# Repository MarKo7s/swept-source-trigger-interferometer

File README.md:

# Swept-source interferometer camera trigger (k-clock)

## Project: DIY k-clock for laser-sweep synchronization

This repository has what you need to build a **k-clock** for applications such as optical coherence tomography (OCT):

1. PCB schematics
2. Firmware for trigger detection
3. SCPI command interface and Python package (**pySSTri**)

You still need the external optics and detectors: swept laser, interferometer, and balanced photodiode (BPD).

## What is a k-clock?

A **k-clock** (swept-source interferometer trigger) produces equally spaced optical-frequency samples across a fixed bandwidth by detecting zero-crossings of the interferogram $V_{\mathrm{BPD}}(\nu)$ and emitting a TTL (~5 V) edge at each crossing. Those edges mark known optical frequencies $\nu$ (or wavelengths) along the sweep.

The raw interferogram rate is set by the optical path-length mismatch between the interferometer arms. Signal conditioning and trigger generation run on a **PSoC 5LP** — a programmable SoC with a 32-bit MCU, configurable analog blocks, and programmable digital logic on one chip. This board digitally **frequency-divides** the BPD/camera trigger train by an arbitrary integer in hardware (no CPU in the divider path). Hosts talk over UART (115200 baud, CRLF). The Python package **pySSTri** wraps that protocol.

## Interferometer working principle

The laser is launched into one port of a 50/50 coupler and sweeps optical frequency $\nu$ at constant speed across a bandwidth $\Delta\nu$. After the first coupler, the field $E_{\mathrm{in}}(\nu)$ is split into $E_1(\nu)$ and $E_2(\nu)$ and recombined in a second coupler. One arm includes an extra fibre delay of length $l_{\mathrm{DLY}}$.

After balanced photodetection (BPD), TIA, and voltage amplification, the electrical interferogram is:

$$
V_{\mathrm{BPD}}(\nu) = V_0 \cdot \cos\left(2\pi\cdot\frac{1}{\mathrm{FSR}}\cdot\nu\right)
$$

$V_{\mathrm{BPD}}$ crosses zero at equally spaced optical frequencies $\nu_n$. The spacing is the **free spectral range**

$$
\mathrm{FSR} = \frac{c}{n\,l_{\mathrm{DLY}}}
\quad [\mathrm{Hz}]
$$

where $\nu$ is optical frequency, $c$ is the vacuum speed of light, and $n$ is the refractive index of the fibre (so the speed in the medium is $c/n$). Those zero crossings define the natural k-clock grid (panel a below).

*Swept-laser Mach–Zehnder interferometer used as a k-clock.*

The BPD sinusoid is conditioned into a TTL (0 → +5 V) pulse train with the same period $\mathrm{FSR}$. Each rising edge at $\nu_n$ can trigger a camera frame (panel b). The number of frames over the sweep is

$$
D_{\nu} = \frac{\Delta\nu}{\mathrm{FSR}}.
$$

This board digitally divides that TTL by an integer $Q$ in hardware, so only every $Q$-th edge is passed to the camera while keeping the same optical-frequency locations. Example with $Q = 4$: twelve raw edges become four divided triggers (panel c).

*(a) Raw BPD interferogram. (b) Rising-edge TTL after conditioning. (c) Same train after divide-by-4 ($Q=4$).*

---

## Installation (Python)

**Tagged release:**

```bash
pip install "pySSTri @ git+https://github.com/MarKo7s/swept-source-trigger-interferometer.git@v1.1.1"
```

With notebook extras:

```bash
pip install "pySSTri[notebooks] @ git+https://github.com/MarKo7s/swept-source-trigger-interferometer.git@v1.1.1"
```

**Editable (dev):**

```bash
git clone git@github.com:MarKo7s/swept-source-trigger-interferometer.git
cd swept-source-trigger-interferometer
pip install -e ".[notebooks]"
```

**Conda:**

```bash
conda create -n pySSTri_env python=3.11 -y
conda activate pySSTri_env
pip install -e ".[notebooks]"
python -m ipykernel install --user --name pySSTri_env --display-name "Python (pySSTri_env)"
```

---

## How to operate

There are two layers:

| Layer | Use when |
| ----- | -------- |
| **Firmware (UART / SCPI)** | Any host language, raw serial, or writing your own driver |
| **Python (`pySSTri`)** | Lab scripts / notebooks — preferred for day-to-day use |

Same baud rate (115200) and the same commands either way. Python methods map 1:1 onto SCPI (e.g. `SetFreqDivision(4)` → `SIG:TRIG:DIV 4`).

The board does **not** start the laser. The laser (or your control software) asserts the sweep gate `sw`; the PSoC only measures and emits camera TTL. How the **host** keeps up with sweeps falls into two patterns.

### Mode A — Asynchronous (poll / pull)

Laser sweeps on its own schedule. The host configures the board once (`SIG:TRIG:DIV`, maybe encoding), then **queries when convenient**: status, last count, frequency, or pull timestamps **after** the sweep (idle). No blocking wait on UART notify.

Typical uses: debugging, notebook checks, slow loops, “did the last sweep look OK?”

```text
  Laser ──► sw low ──► …sweep… ──► sw high
  Host  ·····························► GetSweepStatus? / GetTimestamps?
                                       (poll when idle)
```

```python
board.SetModeNormal()                 # SYS:TRIG:NOT OFF — no end-of-sweep UART dump
board.SetFreqDivision(2)
# … laser sweeps somehow …
while board.GetSweepStatus() == "1":  # optional: wait until idle
    pass
ts, ov, fc = board.GetTimestamps()    # pull buffer after the sweep
```

While `sw` is low, most commands return `ERROR: 1`; `LASER:SWE:STATUS?` still works.

### Mode B — Synchronous (notify / wait)

Enable end-of-sweep notify (`SYS:TRIG:NOT TIME|COUNT|FREQ|ALL|TIMESTAMP`). When each sweep finishes, the board **pushes** a line (or a `TSU` frame) on UART.

Typical pattern: a **watcher thread** blocks on `waitForSignal()` / `readline`; the **main thread** runs the laser (or other work) and syncs with `done.wait()` when the notify arrives — so UART wait does not block the main thread.

```mermaid
sequenceDiagram
    participant Main as Main thread
    participant Watch as Watcher thread
    participant Board as PSoC board
    participant Laser

    Main->>Board: set notify COUNT
    Main->>Watch: start waitForSignal
    Main->>Laser: start_sweep
    Laser->>Board: sw low then high
    Board-->>Watch: notify line
    Watch->>Main: done.set
    Note over Main: done.wait returns
```

```python
import threading

done = threading.Event()

def watch_sweep_done():
    board.waitForSignal()   # blocks only this thread on UART notify
    done.set()

board.SetModeCount()
board.flushSerialBuffer()
threading.Thread(target=watch_sweep_done, daemon=True).start()

laser.start_sweep()         # main owns the sweep / other work
done.wait(timeout=30.0)     # sync when board says sweep finished
```

For timestamp notify on the watcher thread, use `waitTimestamps()` instead of `waitForSignal()`.

| Aspect | Mode A (async) | Mode B (sync) |
| ------ | -------------- | ------------- |
| Notify | `SYS:TRIG:NOT OFF` | `TIME` / `COUNT` / `FREQ` / `ALL` / `TIMESTAMP` |
| Host API | `GetSweepStatus`, `GetTimestamps`, … | watcher: `waitForSignal` / `waitTimestamps`; main: `Event.wait` |
| Timing | Host decides when to ask | Main syncs when end-of-sweep notify arrives |
| Best for | Inspection, scripts | Acquisition loops without blocking main on UART |

Always `flushSerialBuffer()` after changing notify mode so a stale line does not satisfy the next `wait`.

---

## Firmware

### Which project to flash

Firmware is **variant-specific** (polarity / laser). Pick the folder under `psoc5/firmware/` that matches your hardware:

| Project | Role |
| ------- | ---- |
| `PSOC_trigger_firmware_Trigger_Polarity_Low` | **Production** (FW 1.3.1) — active-low LEVEL sweep gate + timestamps |
| `PSOC_trigger_firmware_DEBUG` | Experimental |

Production firmware is tuned for an **active-low** sweep gate. Other lasers or trigger polarities can be supported on request (see [Contact](#contact)).

### Install tools and flash

1. Install [PSoC Programmer](https://softwaretools.infineon.com/tools/com.ifx.tb.tool.psocprogrammer). If it asks to update the kit / MiniProg firmware, allow that, then **close** Programmer.
2. Install [PSoC Creator](https://www.infineon.com/cms/en/design-support/tools/sdk/psoc-software/psoc-creator/) (Cypress / Infineon).
3. In Creator, open the workspace for the project you chose, e.g. production:

   `psoc5/firmware/PSOC_trigger_firmware_Trigger_Polarity_Low/Trigger_PSOC5.cywrk`

4. Connect the board (USB / MiniProg as wired on your PCB).
5. Build if needed, then **Debug → Program**.
6. Verify over UART (115200 baud, CRLF): send `*IDN?` — it should report firmware version and date (e.g. FW 1.3.1). With Python: `board.ID()` after `connect()`.

Host control after flashing: see [Installation (Python)](#installation-python) and `trigger_example.ipynb`.

### Sweep gate (Polarity Low)

The sweep input `sw` is **active-low LEVEL**, not a falling-edge pulse:

- **Sweeping** while `sw` is held low
- **Idle** while `sw` is high

While sweeping, most commands return `ERROR: 1`. Exception: `LASER:SWE:STATUS?` (`1` = sweeping, `0` = idle).

### Command reference

Lines end with `\r\n`. Sets reply `OK` (or `OK - WARNING: …`). Queries reply a value. Errors: `ERROR: 0` (bad command), `ERROR: 1` (busy / sweeping).

| Command                            | Meaning                                       |
| ---------------------------------- | --------------------------------------------- |
| `*IDN?`                            | Identify                                      |
| `SIG:TRIG:DIV <n>` / `?`           | Camera trigger divider (default `2`)          |
| `SIG:TRIG:EVENTS:COUNT?`           | Trigger count last sweep                      |
| `SIG:TRIG:EVENTS:FREQ?`            | Mean trigger rate [Hz] (first→last timestamp) |
| `SIG:TRIG:TIMESTAMP?`              | Pull timestamp buffer (idle only)             |
| `LASER:SWE:TIME?`                  | Sweep duration [µs]                           |
| `LASER:SWE:COUNT?` / `0` / `RESET` | Cumulative sweeps / clear                     |
| `LASER:SWE:STATUS?`                | `1` sweeping / `0` idle                       |
| `SYS:TRIG:NOT <mode>` / `?` | Notify mode: `OFF`, `TIME`, `COUNT`, `FREQ`, `ALL`, `TIMESTAMP` |
| `SYS:TIMESTAMP:DELTAENC <mode>` / `?` | Packing: `OFF`, `UINT8`, `UINT16` (aliases `0`, `1`, `2`) |

### Timestamps

Each camera-trigger edge is stamped by a 24 MHz Timer during the sweep (ISR fill, up to **4000** samples). Values are **µs from sweep start**.

**Typical flow**

1. Optionally set packing: `SYS:TIMESTAMP:DELTAENC UINT16` (see delta encoding below).
2. Run a sweep (or enable `SYS:TRIG:NOT TIMESTAMP` for an automatic dump each sweep).
3. When idle: `SIG:TRIG:TIMESTAMP?` → one ASCII header line + binary payload.

**Wire header** (always the same fields):

```
TSU <n> <ov> <fc> <t0> <enc>\r\n
```

| Field | Meaning                                         |
| ----- | ----------------------------------------------- |
| `n`   | Number of timestamps                            |
| `ov`  | `1` if buffer overflowed or a delta was clamped |
| `fc`  | Hardware event count for the sweep              |
| `t0`  | First sample [µs]                               |
| `enc` | Packing mode (`0` / `1` / `2`) — always last    |

Then the **payload** depends on `enc`:

| `enc` | Name           | Payload                     | Host reconstruct           |
| ----- | -------------- | --------------------------- | -------------------------- |
| `0`   | OFF (absolute) | `n × uint32` LE absolute µs | use as-is                  |
| `1`   | UINT8 deltas   | `(n−1) × uint8` gaps        | `t[0]=t0`, then accumulate |
| `2`   | UINT16 deltas  | `(n−1) × uint16` LE gaps    | same accumulate            |

Delta encoding shrinks UART traffic when consecutive gaps are small. Choose a mode whose **max gap** fits your laser:

| Mode   | Max gap       | Safe if trigger rate |
| ------ | ------------- | -------------------- |
| UINT8  | 255 µs        | **≥ ~3.9 kHz**       |
| UINT16 | 65535 µs      | **≥ ~15 Hz**         |
| OFF    | (full uint32) | any                  |

If a gap is too large for the mode, firmware **clamps** it and sets `ov=1` (lossy). For ~3 kHz SS sources, prefer **UINT16** or **OFF**, not UINT8.

Setting the mode returns a warning with those limits, e.g.:

```
SYS:TIMESTAMP:DELTAENC 2
→ OK - WARNING: max_dt_us=65535 min_freq_hz=15
```

**False triggers:** noisy interferogram / BPD edges can create extra timestamps. A hardware **deglitch** filter is planned but not in this firmware yet — raise the comparator threshold / SNR, or filter bad gaps in software for now.

### Hardware (PCB)

Eagle schematics and board files: `pcb/Eagle_project/Trigger_PSOC5LP`.

---

## Python interface (`pySSTri`)

Example notebook: `trigger_example.ipynb`.

### Connect

```python
from pySSTri import SSTriggerInterferometer

board = SSTriggerInterferometer()   # or COM="COM6"
board.connect()                     # autodiscovers via *IDN? if needed
board.discoverMethods()             # list wrappers
print(board.ID())
```

### Everyday control

See [How to operate](#how-to-operate) for async poll vs sync wait. Short sync example:

```python
board.SetFreqDivision(2)
board.SetModeCount()                # notify: trigger count each sweep
board.flushSerialBuffer()
print(board.waitForSignal())        # blocks for next notify line
print(board.GetSweepStatus())       # "0" / "1"
print(board.GetFrequency(), board.GetSweepTime())
```

### Timestamps (decoded to absolute µs for you)

```python
board.SetTimestampsEncoding(2)      # UINT16 deltas on the wire (FW aliases OK)
# board.SetModeTimestamp()          # optional: auto-dump each sweep
# ts, ov, fc = board.waitTimestamps()

ts, ov, fc = board.GetTimestamps()  # after a sweep, while idle
# ts: uint32 array [µs], regardless of enc in the header
```

`GetTimestamps` / `waitTimestamps` read the `TSU` header’s `enc` field and unpack the payload — you always get absolute times.

---

## Repository layout

```
pySSTri/          Python package
psoc5/firmware/   PSoC Creator projects
pcb/              Eagle schematics
trigger_example.ipynb
scripts/release.py
CITATION.cff      GitHub / Zenodo cite metadata
CITATION.bib      BibTeX for manuscripts
```

---

## Developer notes

### Versioning

The package version is defined in **one place only**: `pyproject.toml` → `[project].version`.

Do **not** edit `pySSTri/__init__.py` on each release. `pySSTri.__version__` is read from pip metadata after install (`importlib.metadata`).

Check the installed version:

```bash
pip show pySSTri
python -c "import pySSTri; print(pySSTri.__version__)"
```

Use [semantic versioning](https://semver.org/): `MAJOR.MINOR.PATCH`.

Firmware has its own identity (`FW_VERSION` / `FW_DATE` in `main.c`, reported by `*IDN?`). Bump that when you change the PSoC image; it is independent of the pySSTri package version.

Default git branch is `main`.

### Releasing a new version

1. Add a `## [X.Y.Z] - YYYY-MM-DD` section at the top of `CHANGELOG.md` (keep `## [Unreleased]` above it for WIP notes).
2. Set `version = "X.Y.Z"` in `pyproject.toml`.
3. Commit everything (clean working tree).
4. From the repo root:

```bash
python scripts/release.py --from-changelog
```

The script reads the version from `pyproject.toml`, pushes `main`, creates annotated git tag `vX.Y.Z`, and pushes the tag. With `--from-changelog`, the tag message is taken from the matching `CHANGELOG.md` section. Override with `--message "..."` if needed.

Dry run (no git changes):

```bash
python scripts/release.py --from-changelog --dry-run
```

Optional GitHub Release page (`gh` CLI):

```bash
gh release create vX.Y.Z --title "pySSTri X.Y.Z" --notes-file CHANGELOG.md
```

After release, others install with:

```bash
pip install "pySSTri @ git+https://github.com/MarKo7s/swept-source-trigger-interferometer.git@vX.Y.Z"
```

**Requirements:** clean working tree; tag `vX.Y.Z` must not already exist on GitHub.

## Contact

Marcos Maestre Morote — [m.maestremorote@uq.edu.au](mailto:m.maestremorote@uq.edu.au)

Questions, bug reports, or requests to adapt the firmware to a different swept laser / sweep-gate polarity are welcome.

## License

This project is licensed under the [MIT License](LICENSE). Copyright (c) 2026 Marcos Maestre Morote.

## Citation

Use these identifiers in the manuscript so Methods, Supplementary, and the bibliography stay consistent.

### Versions to tag

| Item | Value to cite |
| ---- | ------------- |
| Software / archive | **pySSTri v1.1.1** |
| Git tag | `v1.1.1` |
| Zenodo DOI | [10.5281/zenodo.21639219](https://doi.org/10.5281/zenodo.21639219) |
| Production firmware | **Polarity Low 1.3.1** (`*IDN?` / `board.ID()`) |
| BibTeX key | `MaestreMorote2026pySSTri` (see [`CITATION.bib`](CITATION.bib)) |

### BibTeX (drop into your `.bib`)

```bibtex
@software{MaestreMorote2026pySSTri,
  author       = {Maestre Morote, Marcos},
  title        = {{Swept-source interferometer camera trigger (pySSTri)}},
  year         = {2026},
  publisher    = {Zenodo},
  version      = {v1.1.1},
  doi          = {10.5281/zenodo.21639219},
  url          = {https://doi.org/10.5281/zenodo.21639219},
  note         = {Firmware Polarity Low 1.3.1; source https://github.com/MarKo7s/swept-source-trigger-interferometer}
}
```

LaTeX: `\cite{MaestreMorote2026pySSTri}`. Word / EndNote: import the DOI or use the formatted reference below.

### Formatted reference

> Marcos Maestre Morote. *Swept-source interferometer camera trigger (pySSTri)*. Zenodo (2026). Version v1.1.1. https://doi.org/10.5281/zenodo.21639219

### Paste into Methods

Adapt to your tense/house style; keep the cite key and versions:

> Wavelength / optical-frequency sampling during each laser sweep was provided by a fibre Mach–Zehnder k-clock interferometer and balanced photodiode. Zero-crossing edges were conditioned into a TTL train and divided by an integer $Q$ in hardware on a custom PSoC 5LP camera-trigger board. Instrument control used the open-source package pySSTri (v1.1.1; firmware Polarity Low 1.3.1) \cite{MaestreMorote2026pySSTri}.

### Paste into Supplementary

> **Trigger interferometer and camera timing.** The auxiliary k-clock path is a fibre Mach–Zehnder interferometer with fixed delay; the balanced-photodiode interferogram is converted to a TTL pulse train at the free-spectral-range spacing. A PSoC 5LP board performs hardware frequency division of that train and exposes sweep timing over UART (115200 baud, SCPI-like commands). Host software was **pySSTri** v1.1.1 (GitHub tag `v1.1.1`), archived at Zenodo (DOI: 10.5281/zenodo.21639219), with production firmware **Trigger Polarity Low** 1.3.1. Schematics, firmware, and the Python interface are available under the MIT License at https://github.com/MarKo7s/swept-source-trigger-interferometer. Further protocol details (notify vs poll modes, timestamp frames) are documented in the repository README.

GitHub also exposes **Cite this repository** from [`CITATION.cff`](CITATION.cff).

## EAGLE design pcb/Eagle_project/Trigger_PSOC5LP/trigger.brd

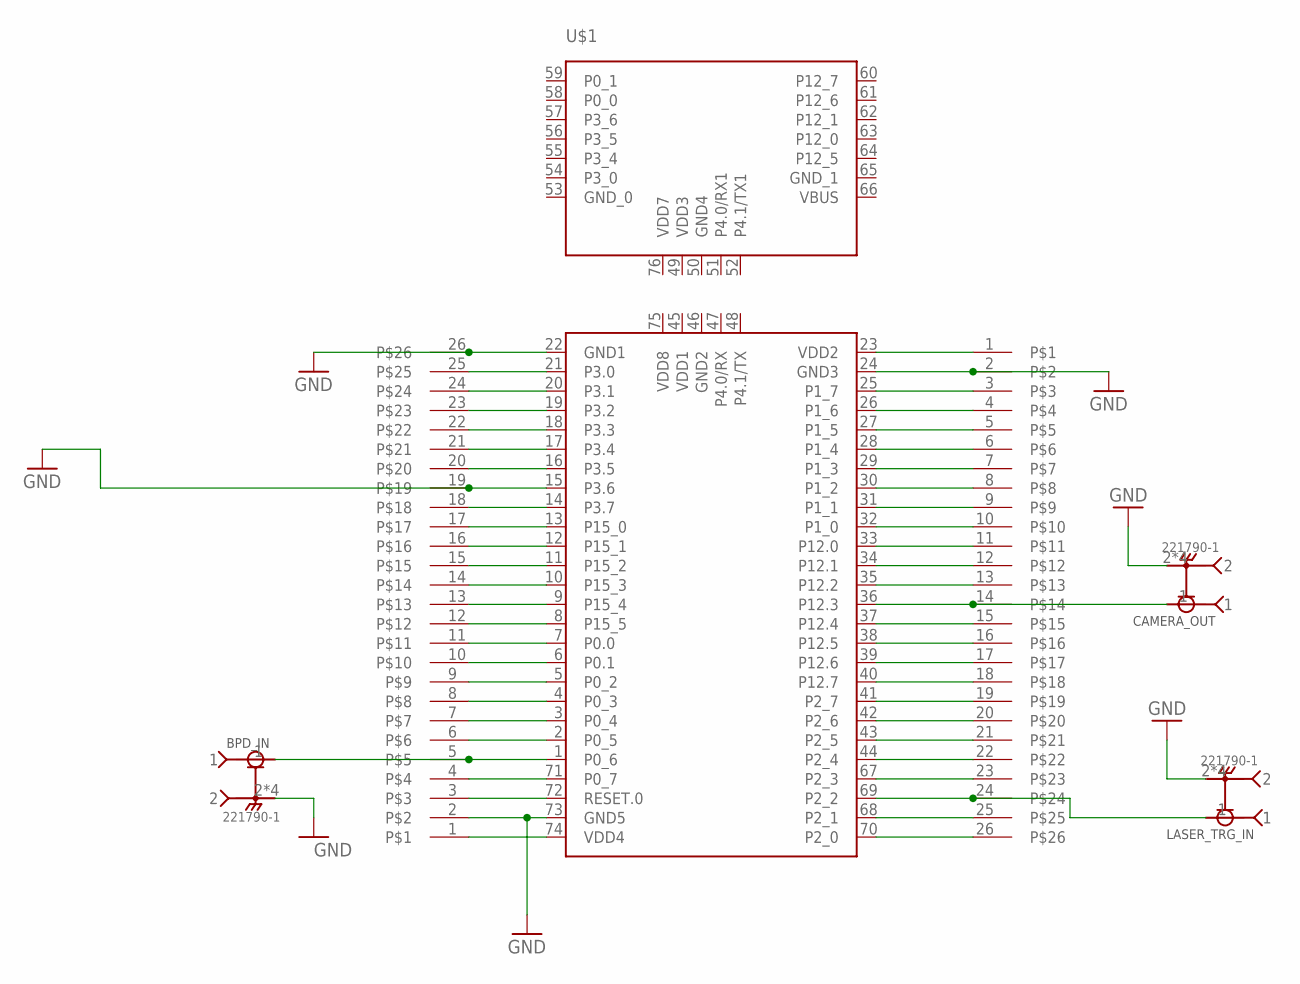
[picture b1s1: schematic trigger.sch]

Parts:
BPD_IN: 221790-1; TE_221790-1
CAMERA_OUT: 221790-1; TE_221790-1
LASER_TRG_IN: 221790-1; TE_221790-1
U$1: CY8CKIT-049-42XX
U$2, U$3: PINHEADER_PSOC5LP; PINHEADER

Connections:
GND: BPD_IN.2, BPD_IN.3 (2), BPD_IN.4 (2), BPD_IN.5 (2), CAMERA_OUT.2, CAMERA_OUT.3 (2), CAMERA_OUT.4 (2), CAMERA_OUT.5 (2), LASER_TRG_IN.2, LASER_TRG_IN.3 (2), LASER_TRG_IN.4 (2), LASER_TRG_IN.5 (2), U$1.15 (P3.6), U$1.22 (GND1), U$1.24 (GND3), U$1.73 (GND5), U$2.2, U$2.19, U$2.26, U$3.2
unnamed: U$1.8 (P15_5), U$2.12
unnamed: U$1.72 (RESET.0), U$2.3
unnamed: U$1.21 (P3.0), U$2.25
unnamed: U$1.20 (P3.1), U$2.24
unnamed: U$1.19 (P3.2), U$2.23
unnamed: U$1.18 (P3.3), U$2.22
unnamed: U$1.17 (P3.4), U$2.21
unnamed: U$1.16 (P3.5), U$2.20
unnamed: U$1.67 (P2_3), U$3.23
unnamed: U$1.14 (P3.7), U$2.18
unnamed: U$1.13 (P15_0), U$2.17
unnamed: U$1.12 (P15_1), U$2.16
unnamed: U$1.11 (P15_2), U$2.15
unnamed: U$1.10 (P15_3), U$2.14
unnamed: U$1.9 (P15_4), U$2.13
unnamed: U$1.7 (P0.0), U$2.11
unnamed: U$1.5 (P0_2), U$2.9
unnamed: U$1.4 (P0_3), U$2.8
unnamed: U$1.3 (P0_4), U$2.7
unnamed: U$1.2 (P0_5), U$2.6
unnamed: BPD_IN.1, U$1.1 (P0_6), U$2.5
unnamed: U$1.71 (P0_7), U$2.4
unnamed: U$1.6 (P0.1), U$2.10
unnamed: U$1.74 (VDD4), U$2.1
unnamed: U$1.23 (VDD2), U$3.1
unnamed: U$1.25 (P1_7), U$3.3
unnamed: U$1.26 (P1_6), U$3.4
unnamed: U$1.27 (P1_5), U$3.5
unnamed: U$1.28 (P1_4), U$3.6
unnamed: U$1.29 (P1_3), U$3.7
unnamed: U$1.30 (P1_2), U$3.8
unnamed: U$1.31 (P1_1), U$3.9
unnamed: U$1.32 (P1_0), U$3.10
unnamed: U$1.33 (P12.0), U$3.11
unnamed: U$1.34 (P12.1), U$3.12
unnamed: U$1.35 (P12.2), U$3.13
unnamed: CAMERA_OUT.1, U$1.36 (P12.3), U$3.14
unnamed: U$1.37 (P12.4), U$3.15
unnamed: U$1.38 (P12.5), U$3.16
unnamed: U$1.39 (P12.6), U$3.17
unnamed: U$1.40 (P12.7), U$3.18
unnamed: U$1.41 (P2_7), U$3.19
unnamed: U$1.42 (P2_6), U$3.20
unnamed: U$1.43 (P2_5), U$3.21
unnamed: U$1.44 (P2_4), U$3.22
unnamed: LASER_TRG_IN.1, U$1.69 (P2_2), U$3.24
unnamed: U$1.68 (P2_1), U$3.25
unnamed: U$1.70 (P2_0), U$3.26

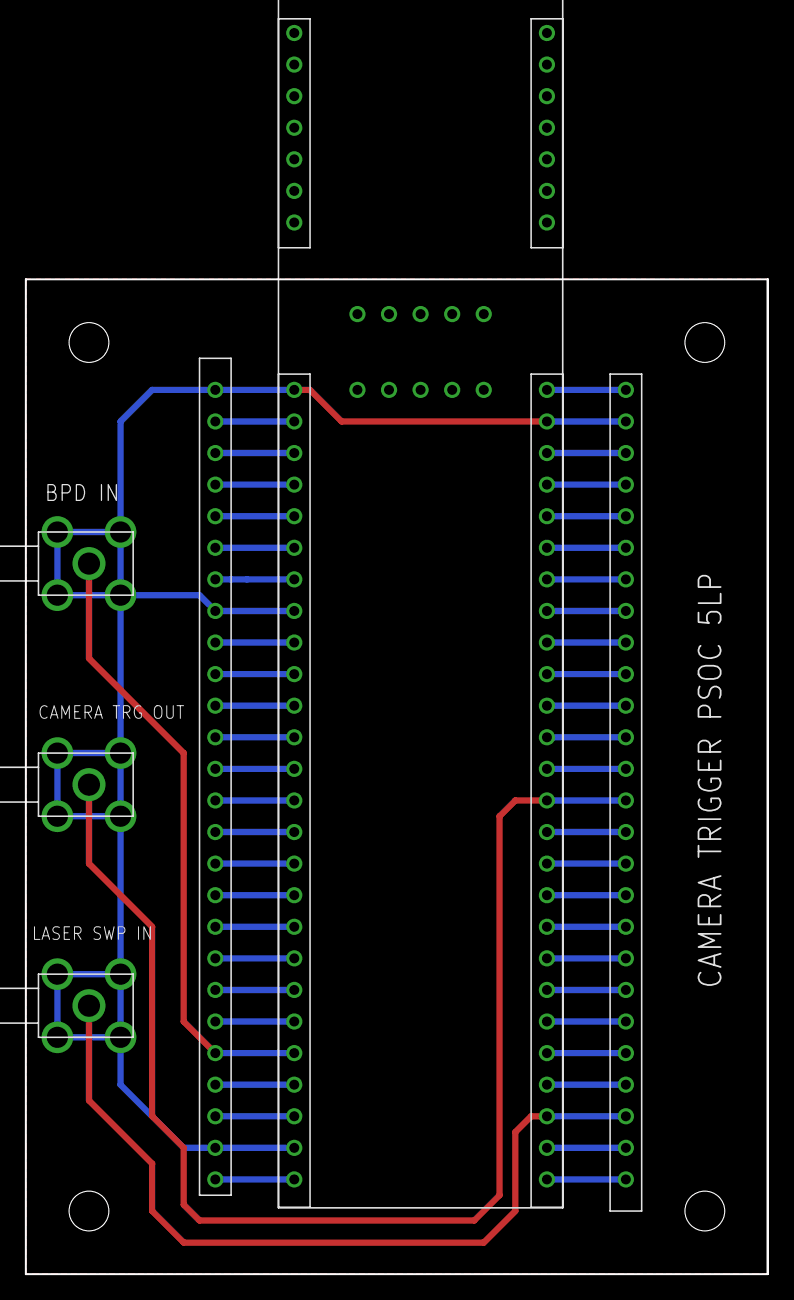
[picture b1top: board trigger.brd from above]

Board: 2 copper layers, 59.7 x 80.0 mm, 6 parts (0 on the bottom side), 49 nets.
